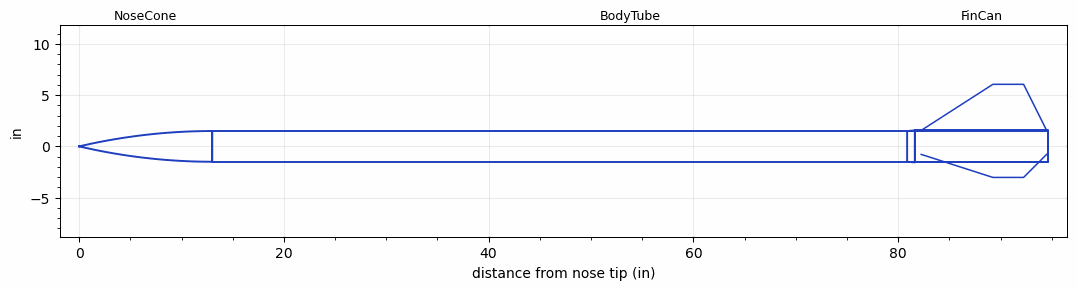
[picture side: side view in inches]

<RASAeroDocument>
 <FileVersion>2</FileVersion>
 <RocketDesign>
  <NoseCone>
   <Length>13</Length>
   <Diameter>3</Diameter>
   <Shape>Tangent Ogive</Shape>
   <BluntRadius>0.125</BluntRadius>
   <Location>0</Location>
  </NoseCone>
  <BodyTube>
   <Length>81.625</Length>
   <Diameter>3</Diameter>
   <Location>13</Location>
  </BodyTube>
  <FinCan>
   <Length>13</Length>
   <Diameter>3.125</Diameter>
   <InsideDiameter>3</InsideDiameter>
   <RailGuideDiameter>0.375</RailGuideDiameter>
   <RailGuideHeight>0.5</RailGuideHeight>
   <Location>94.625</Location>
   <ShoulderLength>0.75</ShoulderLength>
   <Offset>-13</Offset>
   <Fin>
    <Count>3</Count>
    <Chord>12.25</Chord>
    <Span>4.5</Span>
    <SweepDistance>7</SweepDistance>
    <TipChord>3</TipChord>
    <Thickness>0.2</Thickness>
    <Location>12.375</Location>
    <AirfoilSection>Rounded</AirfoilSection>
   </Fin>
  </FinCan>
  <Surface>Smooth (Zero Roughness)</Surface>
  <ModifiedBarrowman>False</ModifiedBarrowman>
  <Turbulence>False</Turbulence>
  <SustainerNozzle>1.3125</SustainerNozzle>
  <UseBooster1>False</UseBooster1>
  <UseBooster2>False</UseBooster2>
  <Comments>Blister
Ray Kinsel
Rocket launched 3 May 2008
ALX1 file rocket data provided by Ray Kinsel

Barometric Altimeter
Altitude = 9026 ft

RASAero II Prediction = 8301 ft
Error = -8.03%
</Comments>
 </RocketDesign>
 <LaunchSite>
  <Altitude>2400</Altitude>
  <Pressure>30.05</Pressure>
  <RodAngle>0</RodAngle>
  <RodLength>10</RodLength>
  <Temperature>80</Temperature>
  <WindSpeed>8</WindSpeed>
 </LaunchSite>
 <Recovery>
  <Altitude1>1000</Altitude1>
  <Altitude2>750</Altitude2>
  <DeviceType1>None</DeviceType1>
  <DeviceType2>Parachute</DeviceType2>
  <Event1>True</Event1>
  <Event2>True</Event2>
  <Size1>1</Size1>
  <Size2>60</Size2>
  <EventType1>Apogee</EventType1>
  <EventType2>Altitude</EventType2>
  <CD1>1.33</CD1>
  <CD2>1.33</CD2>
 </Recovery>
 <SimulationList>
  <Simulation>
   <SustainerEngine>K1075GG  (AMW)</SustainerEngine>
   <SustainerLaunchWt>17.81</SustainerLaunchWt>
   <SustainerNozzleDiameter>1.3125</SustainerNozzleDiameter>
   <SustainerCG>55.25</SustainerCG>
   <SustainerIgnitionDelay>0</SustainerIgnitionDelay>
   <Booster1SeparationDelay>0</Booster1SeparationDelay>
   <Booster1IgnitionDelay>0</Booster1IgnitionDelay>
   <IncludeBooster1>False</IncludeBooster1>
   <Booster2Delay>0</Booster2Delay>
   <IncludeBooster2>False</IncludeBooster2>
   <TimetoApogee>21.5504</TimetoApogee>
   <MaxAltitude>8301.426</MaxAltitude>
   <MaxVelocity>949.4515</MaxVelocity>
  </Simulation>
 </SimulationList>
</RASAeroDocument>
